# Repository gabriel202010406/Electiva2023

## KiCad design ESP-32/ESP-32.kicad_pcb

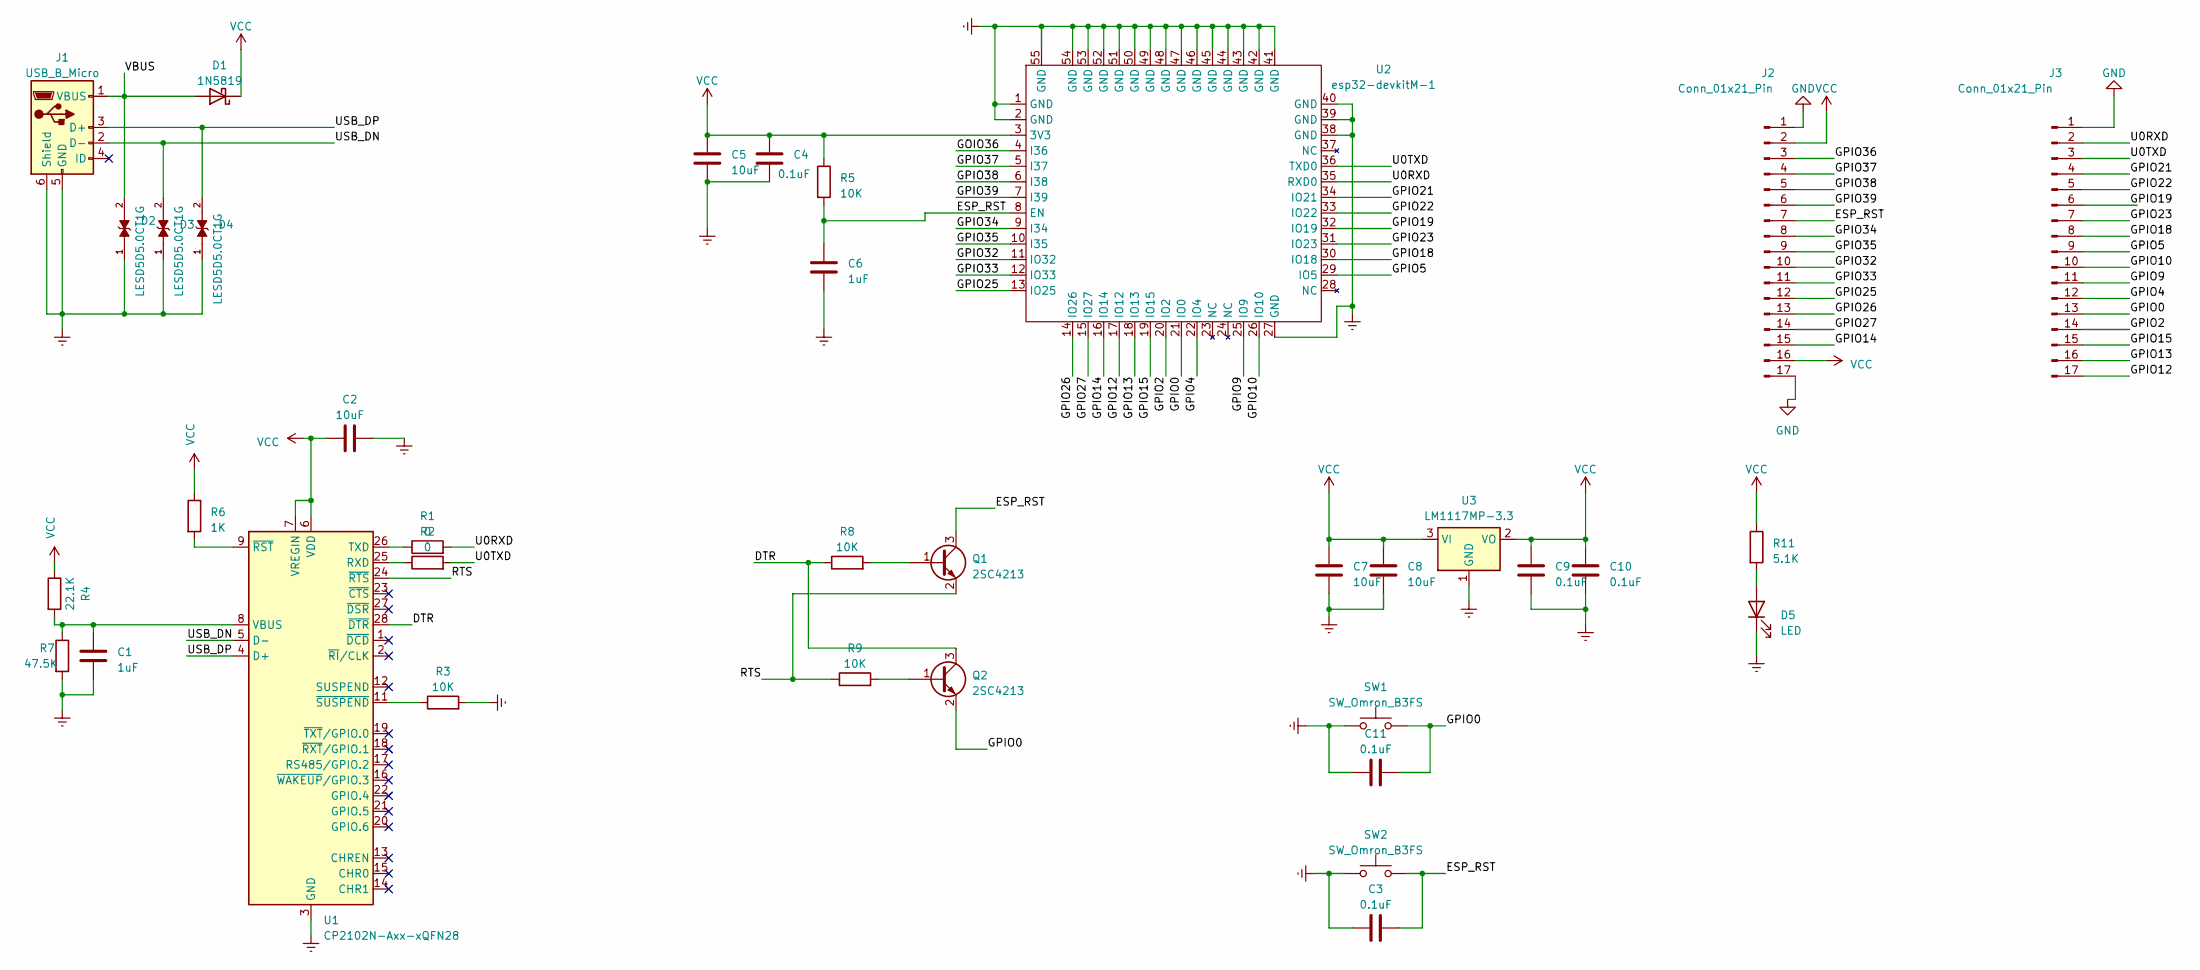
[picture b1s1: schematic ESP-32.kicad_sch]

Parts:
C1, C6: 1uF; C_0805_2012Metric_Pad1.18x1.45mm_HandSolder
C2, C5, C7, C8: 10uF; C_0805_2012Metric_Pad1.18x1.45mm_HandSolder
C3, C4, C9, C10, C11: 0.1uF; C_0805_2012Metric_Pad1.18x1.45mm_HandSolder
D1: 1N5819; D_0805_2012Metric_Pad1.15x1.40mm_HandSolder
D2, D3, D4: LESD5D5.0CT1G; TVS_LESD5D5.0CT1G; PARTREV O
D5: LED; LED_0805_2012Metric_Pad1.15x1.40mm_HandSolder
J1: USB_B_Micro; USB_Micro-B_Molex-105017-0001
J2, J3: Conn_01x21_Pin; PinSocket_1x17_P2.54mm_Vertical
Q1, Q2: 2SC4213; SOT-323_SC-70
R1, R2: 0; R_0805_2012Metric_Pad1.20x1.40mm_HandSolder
R3, R5, R8, R9: 10K; R_0805_2012Metric_Pad1.20x1.40mm_HandSolder
R4: 22.1K; R_0805_2012Metric_Pad1.20x1.40mm_HandSolder
R6: 1K; R_0805_2012Metric_Pad1.20x1.40mm_HandSolder
R7: 47.5K; R_0805_2012Metric_Pad1.20x1.40mm_HandSolder
R11: 5.1K; R_0805_2012Metric_Pad1.20x1.40mm_HandSolder
SW1, SW2: SW_Omron_B3FS; SW_SPST_PTS810
U1: CP2102N-Axx-xQFN28; QFN-28-1EP_5x5mm_P0.5mm_EP3.35x3.35mm
U2: esp32-devkitM-1
U3: LM1117MP-3.3; SOT-223-3_TabPin2

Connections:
/DTR: Q2.3 (C), R8.1, U1.28 (~DTR)
/ESP_RST: C3.2, C6.1, J2.7, Q1.3 (C), R5.2, SW2.2, U2.8 (EN)
/GOIO36: U2.4 (I36)
/GPIO0: C11.2, J3.13, Q2.2 (E), SW1.2, U2.21 (IO0)
/GPIO2: J3.14, U2.20 (IO2)
/GPIO4: J3.12, U2.22 (IO4)
/GPIO5: J3.9, U2.29 (IO5)
/GPIO9: J3.11, U2.25 (IO9)
/GPIO10: J3.10, U2.26 (IO10)
/GPIO12: J3.17, U2.17 (IO12)
/GPIO13: J3.16, U2.18 (IO13)
/GPIO14: J2.15, U2.16 (IO14)
/GPIO15: J3.15, U2.19 (IO15)
/GPIO18: J3.8, U2.30 (IO18)
/GPIO19: J3.6, U2.32 (IO19)
/GPIO21: J3.4, U2.34 (IO21)
/GPIO22: J3.5, U2.33 (IO22)
/GPIO23: J3.7, U2.31 (IO23)
/GPIO25: J2.12, U2.13 (IO25)
/GPIO26: J2.13, U2.14 (IO26)
/GPIO27: J2.14, U2.15 (IO27)
/GPIO32: J2.10, U2.11 (IO32)
/GPIO33: J2.11, U2.12 (IO33)
/GPIO34: J2.8, U2.9 (I34)
/GPIO35: J2.9, U2.10 (I35)
/GPIO36: J2.3
/GPIO37: J2.4, U2.5 (I37)
/GPIO38: J2.5, U2.6 (I38)
/GPIO39: J2.6, U2.7 (I39)
/RTS: Q1.2 (E), R9.1, U1.24 (~RTS)
/U0RXD: J3.2, R1.2, U2.35 (RXD0)
/U0TXD: J3.3, R2.2, U2.36 (TXD0)
/USB_DN: D3.2, J1.2 (D-), U1.5 (D-)
/USB_DP: D4.2, J1.3 (D+), U1.4 (D+)
/VBUS: D1.2 (A), D2.2, J1.1 (VBUS)
Earth: C1.2, C2.1, C3.1, C4.2, C5.2, C6.2, C7.2, C8.2, C9.2, C10.2, C11.1, D2.1, D3.1, D4.1, D5.1 (K), J1.5 (GND), J1.6 (Shield), R3.2, R7.2, SW1.1, SW2.1, U1.3 (GND), U1.29 (GND), U2.1 (GND), U2.2 (GND), U2.27 (GND), U2.38 (GND), U2.39 (GND), U2.40 (GND), U2.41 (GND), U2.42 (GND), U2.43 (GND), U2.44 (GND), U2.45 (GND), U2.46 (GND), U2.47 (GND), U2.48 (GND), U2.49 (GND), U2.50 (GND), U2.51 (GND), U2.52 (GND), U2.53 (GND), U2.54 (GND), U2.55 (GND), U3.1 (GND)
GND: J2.1, J2.17, J3.1
unnamed: D5.2 (A), R11.2
unnamed: Q1.1 (B), R8.2
unnamed: Q2.1 (B), R9.2
unnamed: R2.1, U1.25 (RXD)
unnamed: R1.1, U1.26 (TXD)
unnamed: C1.1, R4.2, R7.1, U1.8 (VBUS)
unnamed: R6.2, U1.9 (~RST)
unnamed: R3.1, U1.11 (~SUSPEND)
VCC: C2.2, C4.1, C5.1, C7.1, C8.1, C9.1, C10.1, D1.1 (K), J2.2, J2.16, R4.1, R5.1, R6.1, R11.1, U1.6 (VDD), U1.7 (VREGIN), U2.3 (3V3), U3.2 (VO), U3.3 (VI)

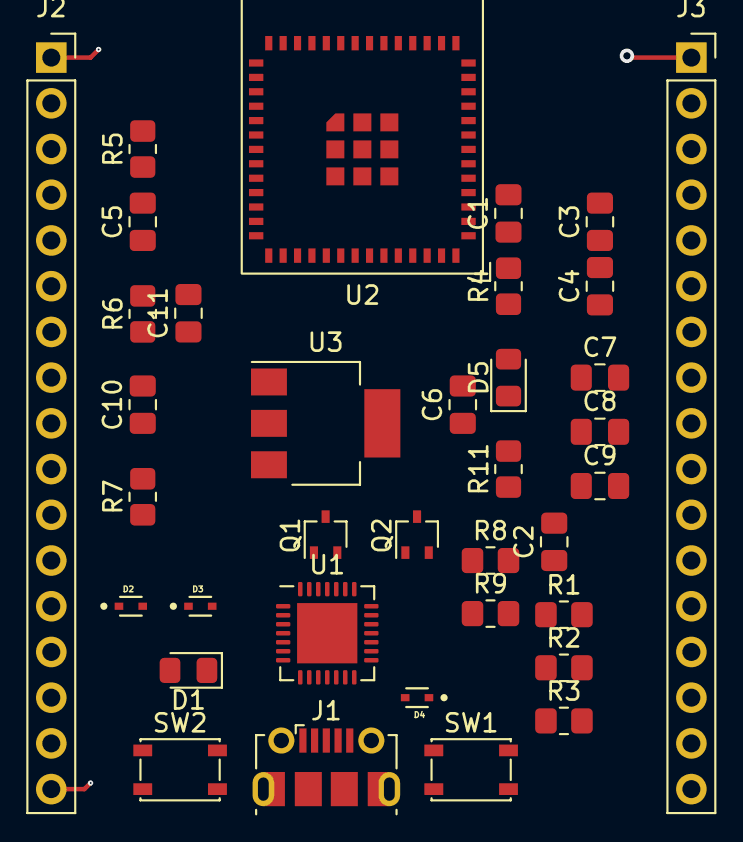
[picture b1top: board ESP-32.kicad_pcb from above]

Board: 4 copper layers, 36 parts (0 on the bottom side), 44 nets.

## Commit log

2023-05-19 subido
2023-05-19 todo arriba
2023-06-03 Revisión 1 del documento
2023-06-03 revison 1 pdf
2023-06-03 Se actualizó la plantilla
2023-06-14 PCB ACTULIZADO
2023-06-14 OTRA VEX
2023-06-14 Se ha añadido el diseño pcb
2023-06-16 pcb actualizado
2023-08-11 proyecto stm
